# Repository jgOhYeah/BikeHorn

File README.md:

# BikeHorn
A "musical" siren for bicycles.

This design was published in the Circuit Notebook section of the [Februrary 2022 issue](https://www.siliconchip.com.au/Issue/2022/February) of the Silicon Chip magazine. Feel free to have a look there if you would like a nice explanation / writeup of the horn's operations and construction.

## Main steps for building and usage
1. Modify the Arduino nano for low power and low voltage usage.
2. Build the circuit - see [BikeHornPCB](BikeHornPCB) for a PCB design. The siren is from an old smoke alarm.
3. 3D print the case.
4. Optimise parameters for each note to be the loudest possible - see [Tuning](Tuning) for details.
5. Generate the tunes to play using [this Musescore plugin](https://github.com/jgOhYeah/TunePlayer/blob/main/extras/MusescorePlugin.md). Paste this into `tunes.h` in the main [BikeHorn sketch](BikeHorn).
6. Upload to the Arduino and test.
7. Mount on bicycle / vehicle and have fun.

See the Silicon Chip section or the [Images directory](Documentation/Images) for relevent diagrams and images of the horn.

A low resolution gif that gives an idea of order of assembly:  

## Extensions
I have attempted to make the firmware fairly modular and most non-core parts have been included as externsions. This allows for easier maintenance and customisation. For more details on enabling, disabling and writing extensions, please see the [extensions documentation](Documentation/Extensions.md).

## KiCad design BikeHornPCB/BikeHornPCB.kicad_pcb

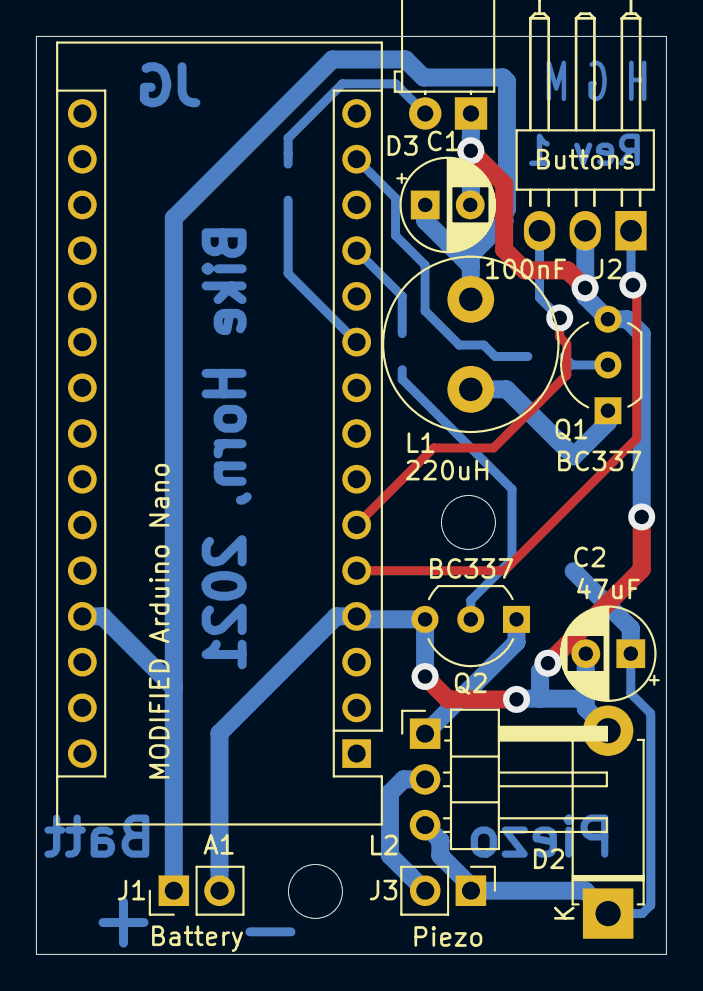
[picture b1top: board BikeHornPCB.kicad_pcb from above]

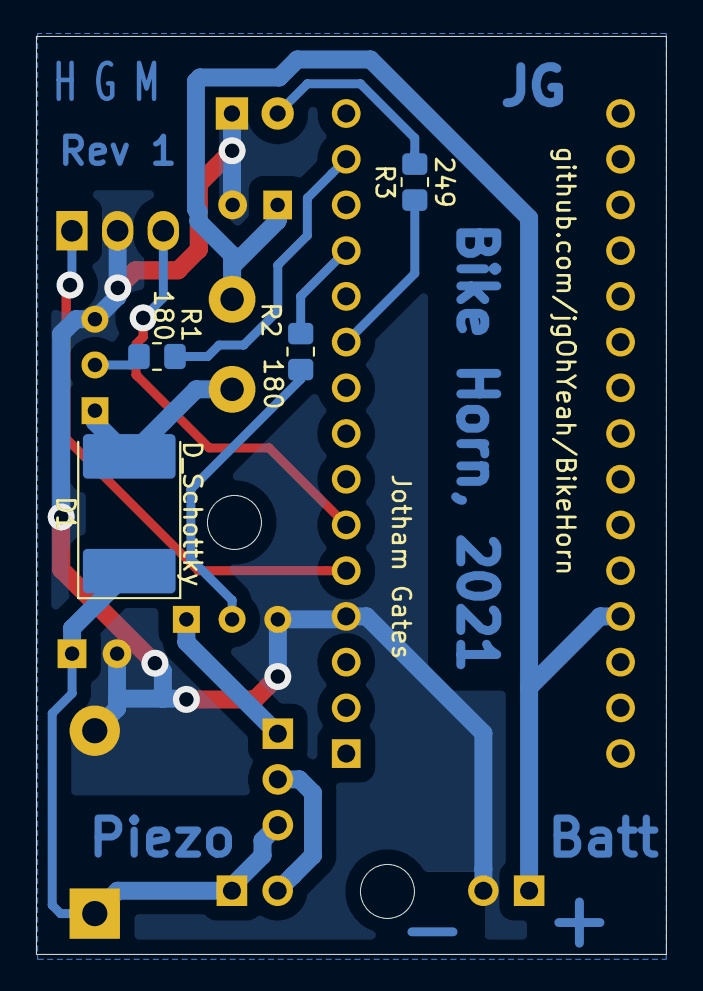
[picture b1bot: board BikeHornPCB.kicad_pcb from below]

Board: 2 copper layers, 35.0 x 51.0 mm, 16 parts (4 on the bottom side), 14 nets.

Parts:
A1: MODIFIED Arduino Nano; Arduino_Nano
C1: 100nF; CP_Radial_D5.0mm_P2.50mm
C2: 47uF; CP_Radial_D5.0mm_P2.50mm
D1: D_Schottky; D_3220_8050Metric
D2: 22V; D_5W_P10.16mm_Horizontal
D3: LED; LED_D5.0mm_Horizontal_O1.27mm_Z3.0mm
J1: Battery; PinHeader_1x02_P2.54mm_Vertical
J2: Buttons; Molex_KK-254_1x03_P2.54mm_Horizontal
J3: Piezo; PinHeader_1x02_P2.54mm_Vertical
L1: 220uH; L_Radial_D9.5mm_P5.00mm_Fastron_07HVP
L2: PiezoDriverCoil; PinHeader_1x03_P2.54mm_Horizontal
Q1, Q2: BC337; TO-92_Inline_Wide
R1, R2: 180; R_0805_2012Metric_Pad1.20x1.40mm_HandSolder
R3: 249; R_0805_2012Metric_Pad1.20x1.40mm_HandSolder

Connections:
+BATT: A1.27, C1.1, J1.1, L1.1
GND: A1.4, C1.2, C2.2, D2.2, D3.1, J1.2, J2.2, Q1.3, Q2.3
unnamed: A1.5, J2.1
unnamed: A1.6, J2.3
unnamed: A1.10, R3.1
unnamed: A1.12, R2.2
unnamed: A1.14, R1.2
unnamed: C2.1, D1.1, D2.1, J3.1, L2.3
unnamed: D1.2, L1.2, Q1.1
unnamed: D3.2, R3.2
unnamed: J3.2, L2.2
unnamed: L2.1, Q2.1
unnamed: Q1.2, R1.1
unnamed: Q2.2, R2.1

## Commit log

2021-06-23 Added files and organising
2021-06-29 Testing with NiMH AAAs
2021-07-08 Switch built into handlebar clamp and stl export
2021-07-10 Added switch in clamp & made intellisense happy
2021-07-12 Renamed tuning.md to readme.md
2021-07-13 Added docs, runtime logging, revised PCB to fix issues from first version built
2021-07-14 Minor formatting improvements
2021-07-15 Formatting & adding optional activation count
2021-07-15 Added eeprom reset and gif
2021-07-16 Documentation
2021-09-18 Improved some comments
2021-09-18 Made diaplyData.py work again, starting adding a varble effect - haven't tested yet
2021-09-19 Warble works but lots of glitches in warble sound
2021-09-19 Warble works with a few less glitches now and new song
2021-10-01 Using interrupts to make warble work without double buffering and without glitches
2021-10-01 stopSound now shuts down timer 1 interrupts
2021-11-25 Added watchdog timer support to reduce embarrassment at low battery levels
2021-12-22 Fixed display data crash on slider adjust, removed adc graph as no longer part of hw
2021-12-27 Added, but not tested reading optimisation settings from eeprom
2021-12-28 Started gui for running optimisation tests
2021-12-28 More work on gui
2021-12-28 Running test in its own thread and hopefully fixed audio shutdown crash
2021-12-29 Added test abort & passing parameters to run test
2021-12-29 Added file menus and help tab
2021-12-29 Got saving and loading files, settings and main testing structure to work
2021-12-29 Added results graph and scroll bar
2021-12-30 Added optimisation graphs & started on optimising
2021-12-30 Testing About Works and Sketch written
2021-12-31 auld lang syne (a bit high)
2022-01-01 Working on analysing data & sketch hopefully works
2022-01-02 Optimisation and gui control implemented. Need to convert to use t1 instead of %
2022-01-02 Implemented transform and display of compiled results
2022-01-03 General GUI improvements
2022-01-03 Uploading to Arduino finally works
2022-01-06 Implemented clipping and eeprom dump
2022-01-09 Added wipe eeprom, tested on windows, converted to grid layout
2022-01-10 Mostly fixed timer values display issues
2022-01-10 Made constants change to improve simplified gradients
2022-01-11 Piecewise functions working on both ends
2022-01-15 Added time taken estimate
2022-01-23 Fixed sometimes not clipping and hopefully stopped multiple error dialogs freezing application
2022-01-25 Added preview to optimiser, bike horn warble sped up, eeprom settings shouldn't be overwritten by logging now
2022-01-27 Cleaning up and documentation
2022-01-27 More documentation
2022-01-28 Added examples, fixed bug opening aborted test file, cleaning up
2022-01-28 Udating main readme
2022-07-01 PCD saved for KiCAD 6, added rescue files that should have been there all along
2022-07-02 Simple extensions framework added, not tested
2022-07-05 Extensions menu works
2022-07-06 Added SOS extension
2022-07-08 Moved midi synth to an extension, added beeps
2022-07-09 Refactored extensions list to an Array object
2022-07-09 Fixed ui beeps and added voltage measurements
2022-08-16 Started adding accelerometer
2022-08-18 Burgler alarm progress, IS_PRESSED macro
2022-08-21 Refactor wakePin, code entry tested
2022-08-22 State machine WIP
2022-08-22 Framework for improved state machine
2022-10-28 Adding names to burgler alarm states (does not compile)
2022-10-30 Added makefile for arduino-cli
2022-11-01 Moving to src folder, fixing includes to compile
2022-11-01 Code entry works
2022-11-06 Countdown with beep and code fail noise works
2022-11-12 Moved images to documentation folder, code to src folder
2022-11-15 Added siren and siren code entry
2022-12-20 Burlger alarm Library ordering changed to allow latest queue library to work
2022-12-30 accelerometer null hypothesis works
2023-01-26 Alarm movement detection & simple triggering works
2023-01-27 Button wakes up alarm
2023-06-20 Implemented various states (old changes not committed)
2023-06-27 Fixed ADC not being turned on to measure battery voltages
2024-02-18 Adapted to Nguyen's PCB. Tested on trike today.
2024-02-23 Fixed optimiser boost duty, added delay to allow 32u4 reprogramming
2024-02-23 Correcting modification dates
